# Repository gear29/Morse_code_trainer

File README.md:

This is a led morse code trainer that will have two buttons to show . and - and then will illuminate the led corresponding to a letter then put that on the screen 
This works by using 2 buttons going into a ras pi which computes the input and turns it into a output going into the display or one of the 4 led controlers
They then output the signal into one of 30 led's two of which are for testing in the code

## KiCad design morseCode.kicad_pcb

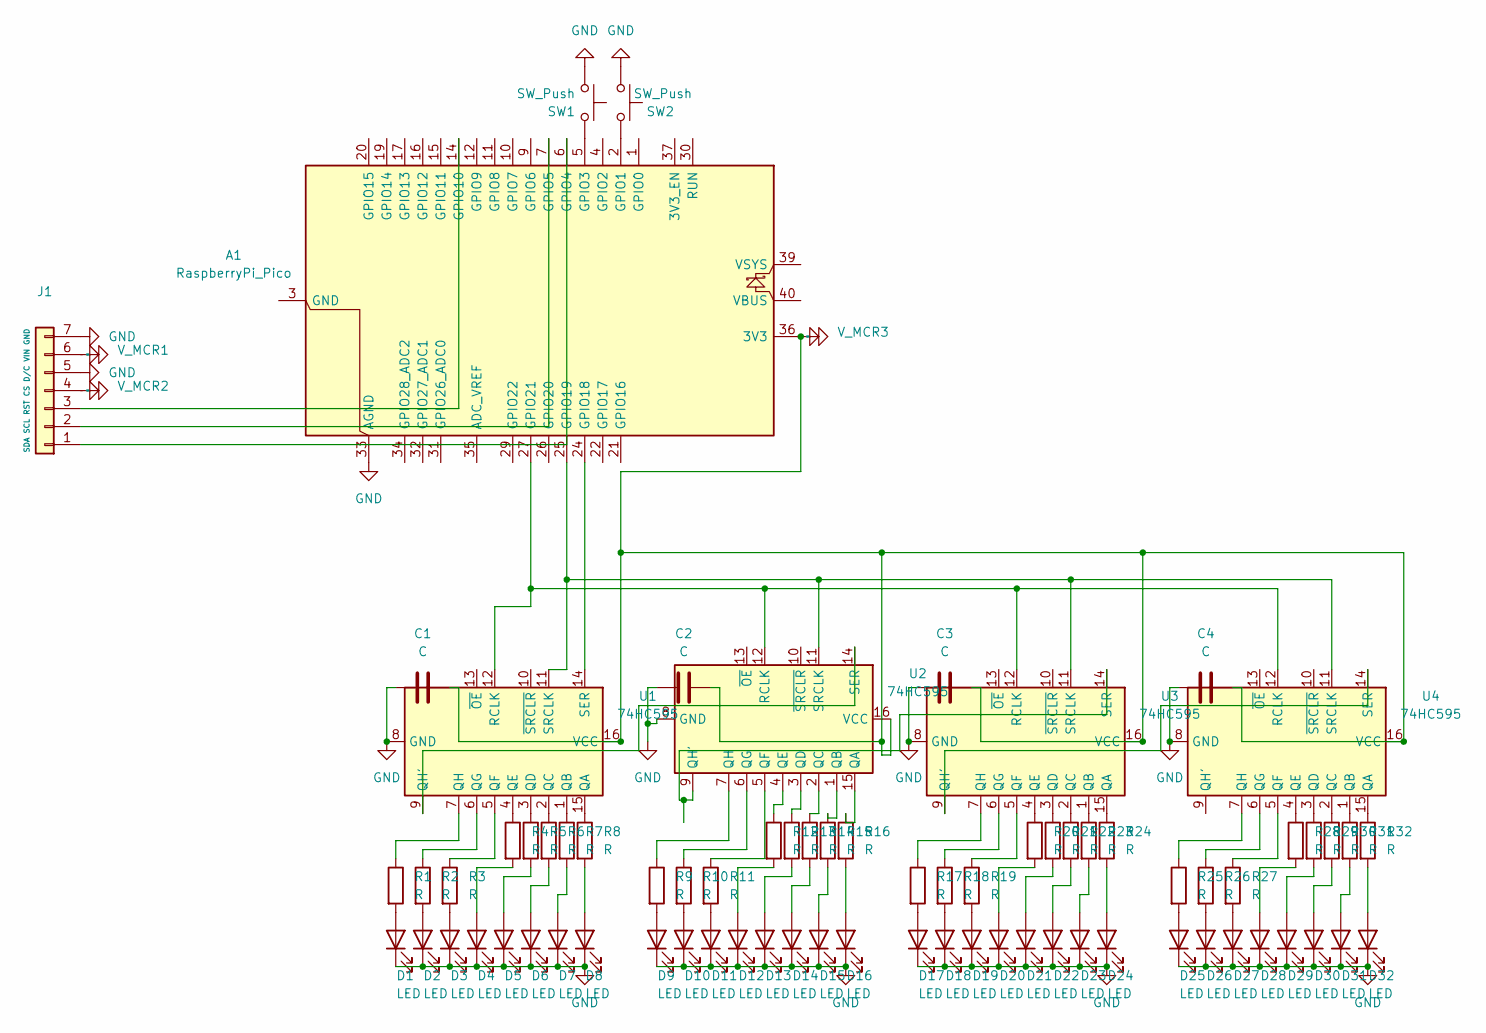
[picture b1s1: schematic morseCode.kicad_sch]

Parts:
A1: RaspberryPi_Pico; RaspberryPi_Pico_Common_Unspecified
C1, C2, C3, C4: C; C_Disc_D5.0mm_W2.5mm_P5.00mm
D1, D2, D3, D4, D5, D6, D7, D8, D9, D10, D11, D12, D13, D14, D15, D16, D17, D18, D19, D20, D21, D22, D23, D24, D25, D26, D27, D28, D29, D30, D31, D32: LED; LED_D5.0mm
J1: SDA SCL RST CS D/C VIN GND; Adafruit_SSD1306
R1, R2, R3, R4, R5, R6, R7, R8, R9, R10, R11, R12, R13, R14, R15, R16, R17, R18, R19, R20, R21, R22, R23, R24, R25, R26, R27, R28, R29, R30, R31, R32: R; R_Axial_DIN0207_L6.3mm_D2.5mm_P10.16mm_Horizontal
SW1, SW2: SW_Push; SW_PUSH_6mm
U1, U2, U3, U4: 74HC595; DIP-16_W7.62mm
V_MCR1, V_MCR2, V_MCR3: (no value)

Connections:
GND: A1.33 (AGND), C1.1, C2.1, C3.1, C4.1, D1.1 (K), D2.1 (K), D3.1 (K), D4.1 (K), D5.1 (K), D6.1 (K), D7.1 (K), D8.1 (K), D9.1 (K), D10.1 (K), D11.1 (K), D12.1 (K), D13.1 (K), D14.1 (K), D15.1 (K), D16.1 (K), D17.1 (K), D18.1 (K), D19.1 (K), D20.1 (K), D21.1 (K), D22.1 (K), D23.1 (K), D24.1 (K), D25.1 (K), D26.1 (K), D27.1 (K), D28.1 (K), D29.1 (K), D30.1 (K), D31.1 (K), D32.1 (K), J1.5, J1.7, SW1.1, SW2.1, U1.8 (GND), U2.8 (GND), U3.8 (GND), U4.8 (GND)
unnamed: A1.36 (3V3), C1.2, C2.2, C3.2, C4.2, U1.16 (VCC), U2.16 (VCC), U3.16 (VCC), U4.16 (VCC), V_MCR3.
unnamed: A1.3 (GND), A1.8 (GND), A1.13 (GND), A1.18 (GND), A1.23 (GND), A1.28 (GND), A1.38 (GND)
unnamed: A1.2 (GPIO1), SW2.2
unnamed: A1.5 (GPIO3), SW1.2
unnamed: A1.6 (GPIO4), J1.1
unnamed: A1.7 (GPIO5), J1.2
unnamed: A1.14 (GPIO10), J1.3
unnamed: A1.24 (GPIO18), U1.14 (SER)
unnamed: A1.25 (GPIO19), U1.11 (SRCLK), U2.11 (SRCLK), U3.11 (SRCLK), U4.11 (SRCLK)
unnamed: A1.27 (GPIO21), U1.12 (RCLK), U2.12 (RCLK), U3.12 (RCLK), U4.12 (RCLK)
unnamed: D1.2 (A), R1.2
unnamed: D2.2 (A), R2.2
unnamed: D3.2 (A), R3.2
unnamed: D4.2 (A), R4.2
unnamed: D5.2 (A), R5.2
unnamed: D6.2 (A), R6.2
unnamed: D7.2 (A), R7.2
unnamed: D8.2 (A), R8.2
unnamed: D9.2 (A), R9.2
unnamed: D10.2 (A), R10.2
unnamed: D11.2 (A), R11.2
unnamed: D12.2 (A), R12.2
unnamed: D13.2 (A), R13.2
unnamed: D14.2 (A), R14.2
unnamed: D15.2 (A), R15.2
unnamed: D16.2 (A), R16.2
unnamed: D17.2 (A), R17.2
unnamed: D18.2 (A), R18.2
unnamed: D19.2 (A), R19.2
unnamed: D20.2 (A), R20.2
unnamed: D21.2 (A), R21.2
unnamed: D22.2 (A), R22.2
unnamed: D23.2 (A), R23.2
unnamed: D24.2 (A), R24.2
unnamed: D25.2 (A), R25.2
unnamed: D26.2 (A), R26.2
unnamed: D27.2 (A), R27.2
unnamed: D28.2 (A), R28.2
unnamed: D29.2 (A), R29.2
unnamed: D30.2 (A), R30.2
unnamed: D31.2 (A), R31.2
unnamed: D32.2 (A), R32.2
unnamed: J1.4, V_MCR2.
unnamed: J1.6, V_MCR1.
unnamed: R8.1, U1.15 (QA)
unnamed: R7.1, U1.1 (QB)
unnamed: R6.1, U1.2 (QC)
unnamed: R5.1, U1.3 (QD)
unnamed: R4.1, U1.4 (QE)
unnamed: R3.1, U1.5 (QF)
unnamed: R2.1, U1.6 (QG)
unnamed: U1.9 (QH'), U2.14 (SER)
unnamed: R1.1, U1.7 (QH)
unnamed: R16.1, U2.15 (QA)
unnamed: R15.1, U2.1 (QB)
unnamed: R14.1, U2.2 (QC)
unnamed: R13.1, U2.3 (QD)
unnamed: R12.1, U2.4 (QE)
unnamed: R11.1, U2.5 (QF)
unnamed: R10.1, U2.6 (QG)
unnamed: U2.9 (QH'), U3.14 (SER)
unnamed: R9.1, U2.7 (QH)
unnamed: R24.1, U3.15 (QA)
unnamed: R23.1, U3.1 (QB)
unnamed: R22.1, U3.2 (QC)
unnamed: R21.1, U3.3 (QD)
unnamed: R20.1, U3.4 (QE)
unnamed: R19.1, U3.5 (QF)
unnamed: R18.1, U3.6 (QG)
unnamed: U3.9 (QH'), U4.14 (SER)
unnamed: R17.1, U3.7 (QH)
unnamed: R32.1, U4.15 (QA)
unnamed: R31.1, U4.1 (QB)
unnamed: R30.1, U4.2 (QC)
unnamed: R29.1, U4.3 (QD)
unnamed: R28.1, U4.4 (QE)
unnamed: R27.1, U4.5 (QF)
unnamed: R26.1, U4.6 (QG)
unnamed: R25.1, U4.7 (QH)

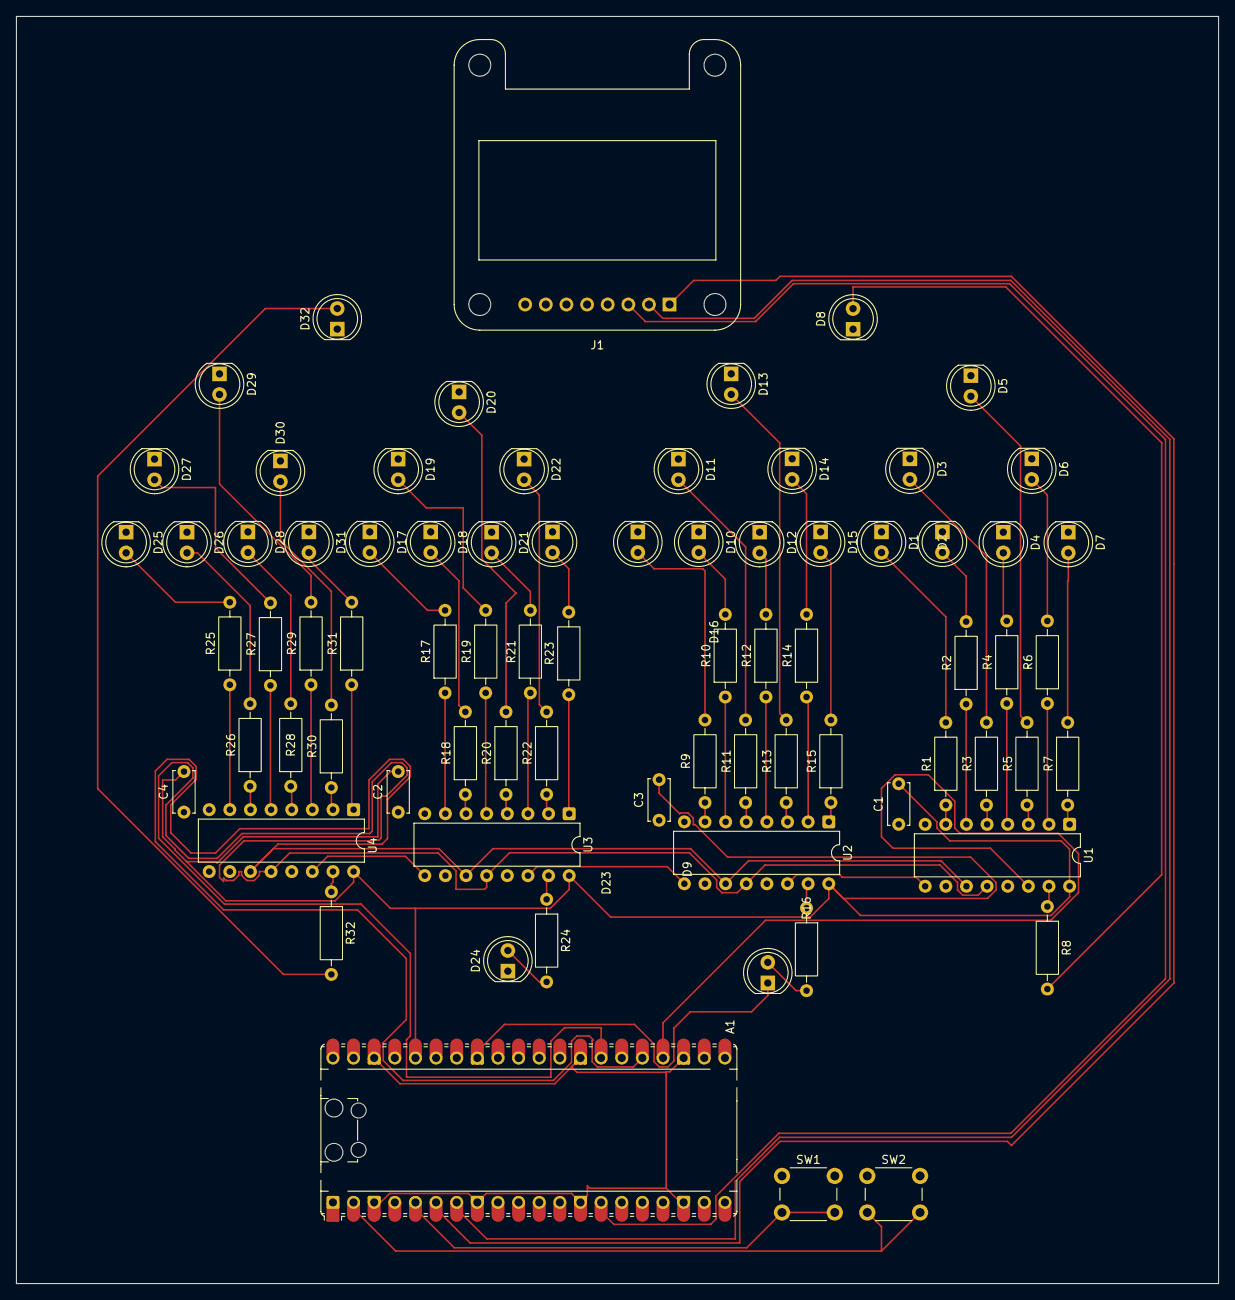
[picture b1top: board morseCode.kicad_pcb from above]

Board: 2 copper layers, 148.0 x 156.0 mm, 76 parts (0 on the bottom side), 78 nets.
